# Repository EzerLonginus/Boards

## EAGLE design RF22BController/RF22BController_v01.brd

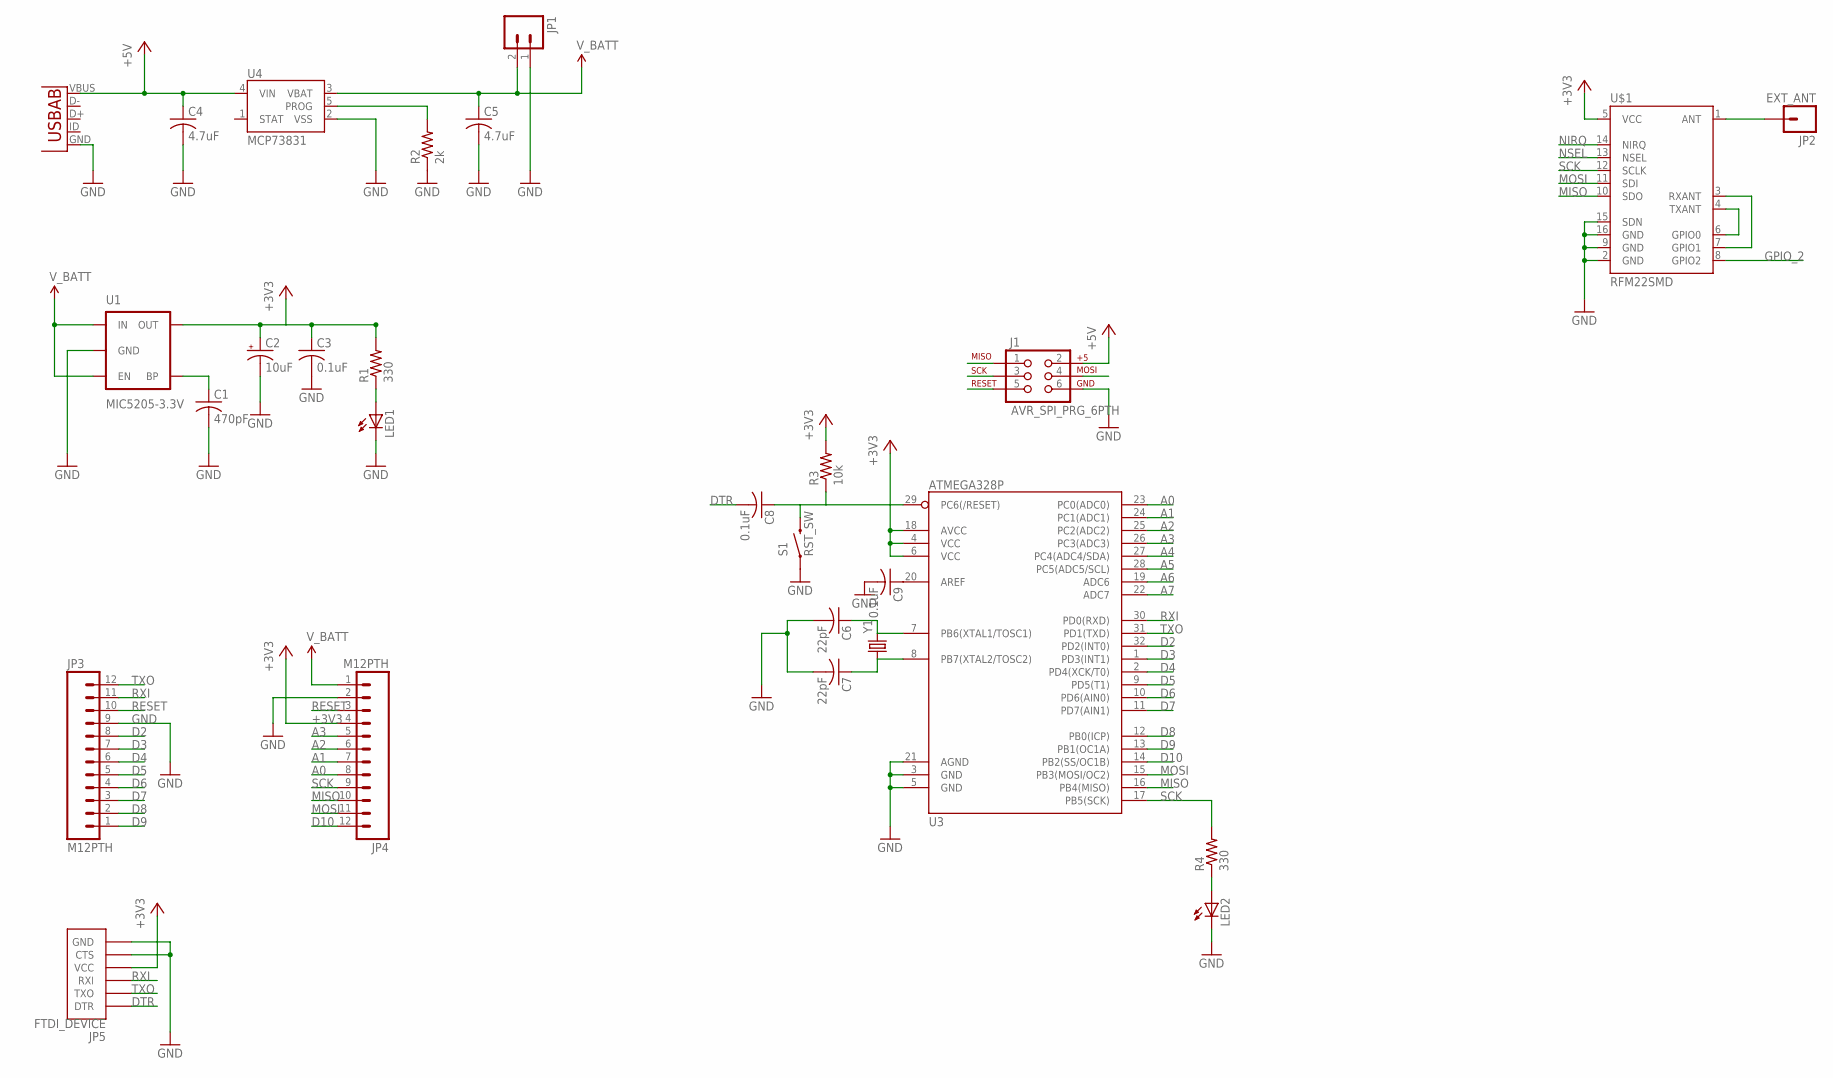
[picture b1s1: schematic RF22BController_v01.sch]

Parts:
C1: 470pF; C0805
C2: 10uF; CT6032
C3, C8, C9: 0.1uF; C0805
C4, C5: 4.7uF; C0805
C6, C7: 22pF; C0805
J1: AVR_SPI_PRG_6PTH; 2X3
JP1: M02-JST-2MM-SMT; JST-2-SMD
JP2: EXT_ANT; 1X01
JP3, JP4: M12PTH; 1X12
JP5: FTDI_DEVICE; FTDI_DEVICE_SIDE
LED1, LED2: LEDCHIP-LED0603; CHIP-LED0603
R1, R4: 330; M0805
R2: 2k; M0805
R3: 10k; M0805
S1: RST_SW; TACTILE_SWITCH_TALL
U1: MIC5205-3.3V; SOT23-5
U2: USB-AB; USB-AB-MICRO-SMD
U3: ATMEGA328P; TQFP32-08
U4: MCP73831; SOT23-5
U$1: RFM22SMD; RFM22-XXX-S2
Y1: CRYSTALTXC-7A; CRYSTAL-TXC-7A

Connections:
+3V3: C2.+, C3.1, JP4.4, JP5.P$4 (VCC), R1.2, R3.2, U1.5 (OUT), U3.4 (VCC), U3.6 (VCC), U3.18 (AVCC), U$1.5 (VCC)
+5V: C4.1, J1.2, U2.VBUS, U4.4 (VIN)
A0: JP4.8, U3.23 (PC0(ADC0))
A1: JP4.7, U3.24 (PC1(ADC1))
A2: JP4.6, U3.25 (PC2(ADC2))
A3: JP4.5, U3.26 (PC3(ADC3))
A4: U3.27 (PC4(ADC4/SDA))
A5: U3.28 (PC5(ADC5/SCL))
A6: U3.19 (ADC6)
A7: U3.22 (ADC7)
D2: JP3.8, U3.32 (PD2(INT0))
D3: JP3.7, U3.1 (PD3(INT1))
D4: JP3.6, U3.2 (PD4(XCK/T0))
D5: JP3.5, U3.9 (PD5(T1))
D6: JP3.4, U3.10 (PD6(AIN0))
D7: JP3.3, U3.11 (PD7(AIN1))
D8: JP3.2, U3.12 (PB0(ICP))
D9: JP3.1, U3.13 (PB1(OC1A))
D10: JP4.12, U3.14 (PB2(SS/OC1B))
DTR: C8.2, JP5.P$1 (DTR)
GND: C1.2, C2.-, C3.2, C4.2, C5.2, C6.2, C7.2, C9.2, J1.6, JP1.1 (2), JP3.9, JP4.2, JP5.P$5 (CTS), JP5.P$6 (GND), LED1.C, LED2.C, R2.1, S1.A2 (1), U1.2 (GND), U2.GND, U3.3 (GND), U3.5 (GND), U3.21 (AGND), U4.2 (VSS), U$1.2 (GND), U$1.9 (GND), U$1.15 (SDN), U$1.16 (GND)
GPIO_2: U$1.8 (GPIO2)
MISO: J1.1, JP4.10, U3.16 (PB4(MISO)), U$1.10 (SDO)
MOSI: J1.4, JP4.11, U3.15 (PB3(MOSI/OC2)), U$1.11 (SDI)
unnamed: C1.1, U1.4 (BP)
unnamed: LED1.A, R1.1
unnamed: U$1.3 (RXANT), U$1.7 (GPIO1)
unnamed: U$1.4 (TXANT), U$1.6 (GPIO0)
unnamed: R2.2, U4.5 (PROG)
unnamed: C9.1, U3.20 (AREF)
unnamed: JP2.1, U$1.1 (ANT)
unnamed: C6.1, U3.7 (PB6(XTAL1/TOSC1)), Y1.P$2 (2)
unnamed: C7.1, U3.8 (PB7(XTAL2/TOSC2)), Y1.P$1 (1)
unnamed: LED2.A, R4.1
NIRQ: U$1.14 (NIRQ)
NSEL: U$1.13 (NSEL)
RESET: C8.1, J1.5, JP3.10, JP4.3, R3.1, S1.B2 (2), U3.29 (PC6(/RESET))
RXI: JP3.11, JP5.P$3 (RXI), U3.30 (PD0(RXD))
SCK: J1.3, JP4.9, R4.2, U3.17 (PB5(SCK)), U$1.12 (SCLK)
TXO: JP3.12, JP5.P$2 (TXO), U3.31 (PD1(TXD))
V_BATT: C5.1, JP1.2 (1), JP4.1, U1.1 (IN), U1.3 (EN), U4.3 (VBAT)

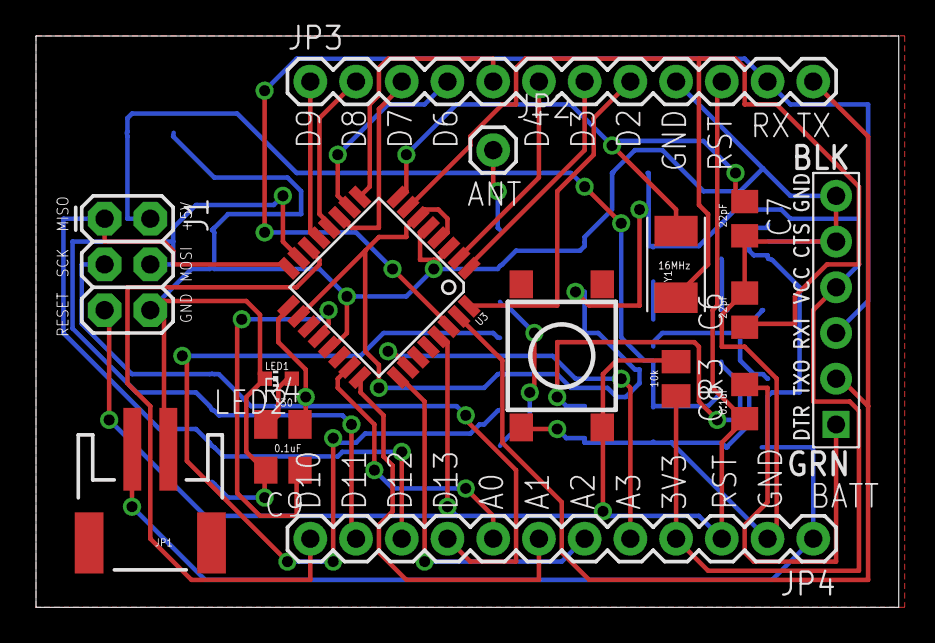
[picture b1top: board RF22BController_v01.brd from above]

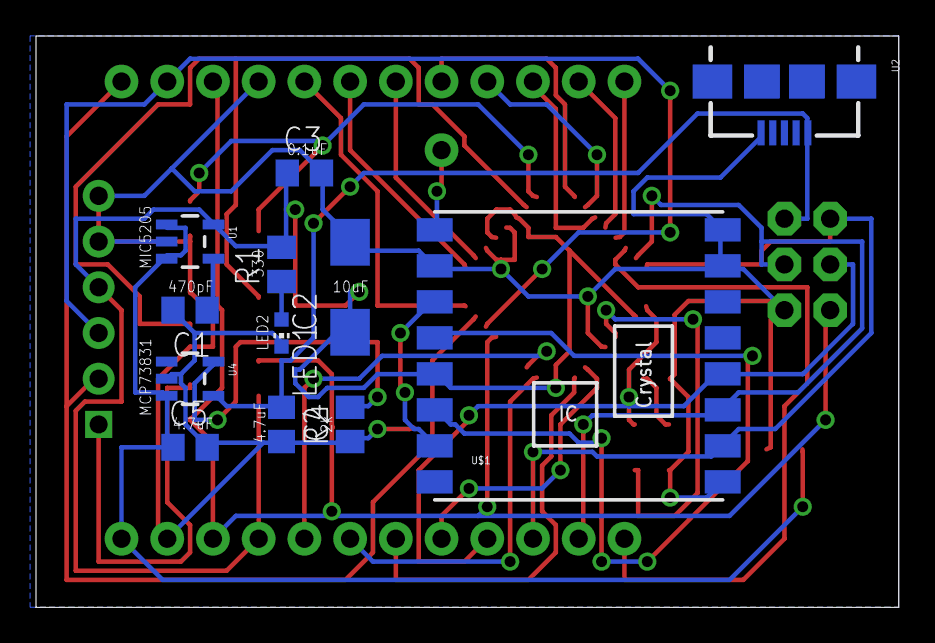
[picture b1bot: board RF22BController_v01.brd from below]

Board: 2 copper layers, 47.9 x 31.7 mm, 28 parts (12 on the bottom side), 34 nets.

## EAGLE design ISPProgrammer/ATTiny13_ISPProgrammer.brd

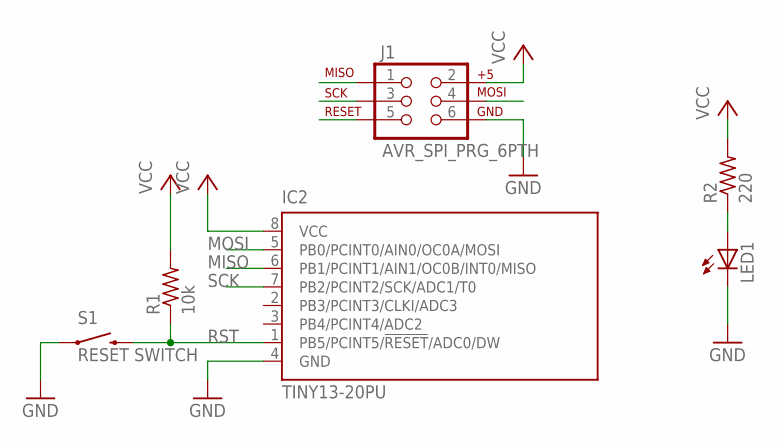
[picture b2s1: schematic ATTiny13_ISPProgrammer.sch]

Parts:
IC2: TINY13-20PU; DIL08
J1: AVR_SPI_PRG_6PTH; 2X3
LED1: LED-3MM-NO_SILK; LED3MM-NS
R1: 10k; 0207/10
R2: 220; 0207/10
S1: RESET SWITCH; TACTILE-PTH

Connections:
GND: IC2.4 (GND), J1.6, LED1.K (C), S1.1
MISO: IC2.6 (PB1/PCINT1/AIN1/OC0B/INT0/MISO), J1.1
MOSI: IC2.5 (PB0/PCINT0/AIN0/OC0A/MOSI), J1.4
unnamed: LED1.A, R2.1
RST: IC2.1 (PB5/PCINT5/!RESET!/ADC0/DW), J1.5, R1.1, S1.3 (2)
SCK: IC2.7 (PB2/PCINT2/SCK/ADC1/T0), J1.3
VCC: IC2.8 (VCC), J1.2, R1.2, R2.2

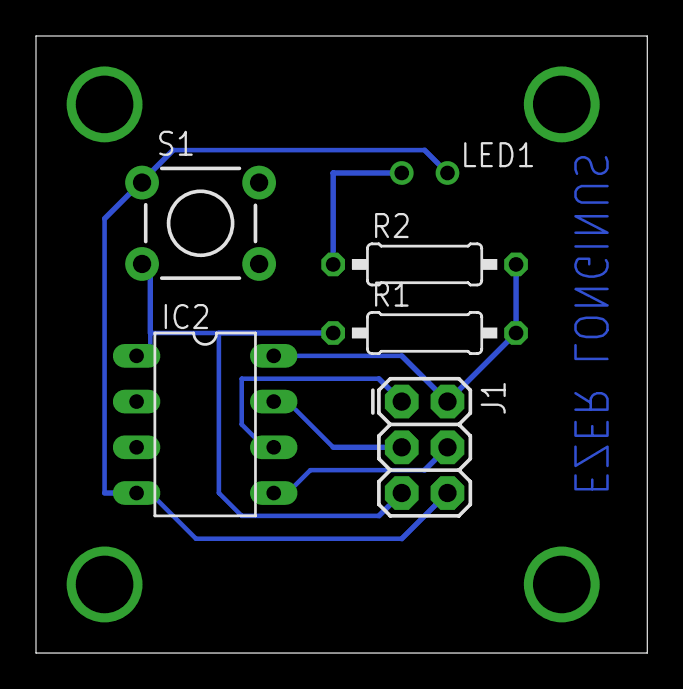
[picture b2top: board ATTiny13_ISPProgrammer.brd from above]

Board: 2 copper layers, 34.0 x 34.3 mm, 6 parts (0 on the bottom side), 7 nets.

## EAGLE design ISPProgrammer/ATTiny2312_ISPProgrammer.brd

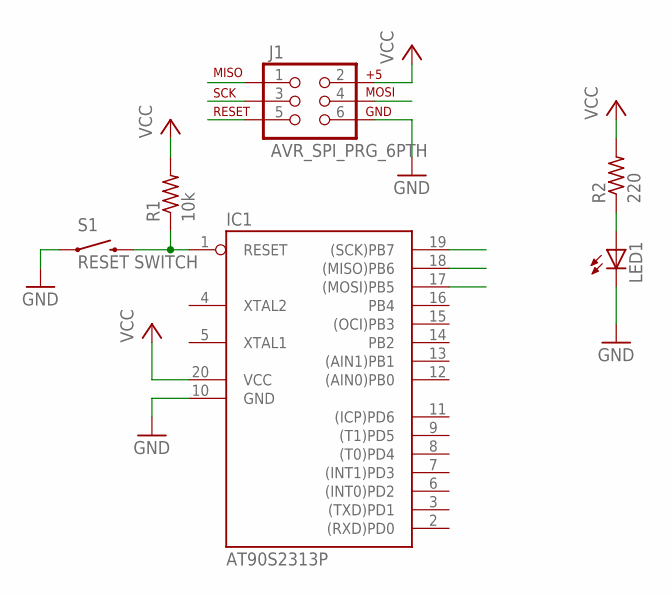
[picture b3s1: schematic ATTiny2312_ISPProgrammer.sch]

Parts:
IC1: AT90S2313P; DIL20
J1: AVR_SPI_PRG_6PTH; 2X3
LED1: LED-3MM-NO_SILK; LED3MM-NS
R1: 10k; 0207/10
R2: 220; 0207/10
S1: RESET SWITCH; TACTILE-PTH

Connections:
GND: IC1.10 (GND), J1.6, LED1.K (C), S1.1
MISO: IC1.18 ((MISO)PB6), J1.1
MOSI: IC1.17 ((MOSI)PB5), J1.4
unnamed: LED1.A, R2.1
RST: IC1.1 (RESET), J1.5, R1.1, S1.3 (2)
SCK: IC1.19 ((SCK)PB7), J1.3
VCC: IC1.20 (VCC), J1.2, R1.2, R2.2

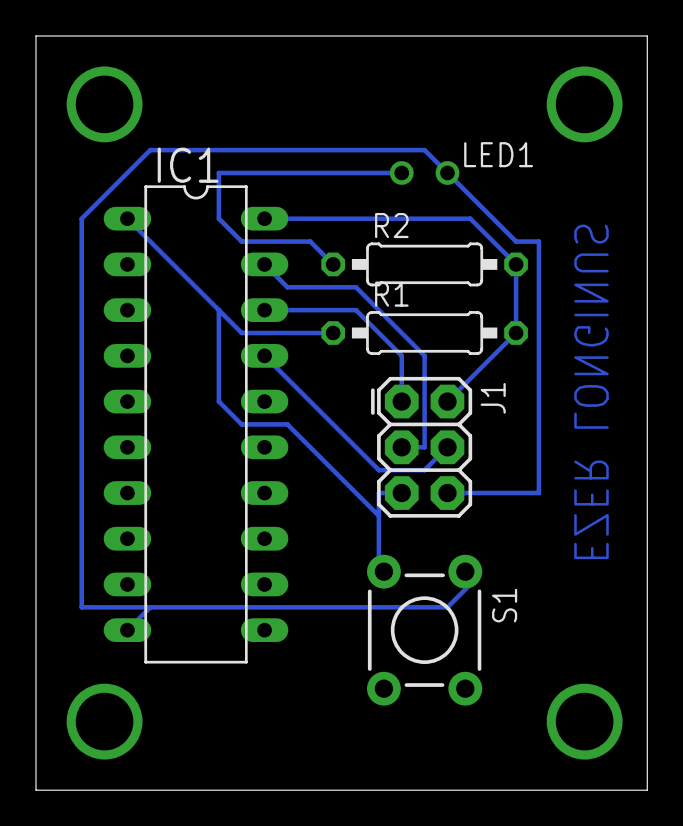
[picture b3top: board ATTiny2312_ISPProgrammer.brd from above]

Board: 2 copper layers, 34.0 x 41.9 mm, 6 parts (0 on the bottom side), 7 nets.

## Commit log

2013-06-07 First upload of AVRTester, ISPProgrammer, and RF22BController

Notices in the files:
parts and their libraries:
SparkFun-Connectors: Licensing: CC v3.0 Share-Alike You are welcome to use this library for commercial purposes.
